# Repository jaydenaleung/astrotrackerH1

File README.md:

# Astrotracker H1
Astrotracker H1 is a DIY star tracker camera mount for astrophotography, made to open access to astrophotography without needing to purchase a more expensive star tracker. Includes a multi-axis rotational gimbal, automatic North Pole alignment, and possible upcoming GoTo integration.

FULL VIDEO DEMO: [https://youtu.be/irbhYrVtJVo](https://youtu.be/irbhYrVtJVo)

Onshape (CAD Model) Link: [https://cad.onshape.com/documents/bffc36d0f5bca770a27c02a3/w/2a2e8752598234cf6c653f02/e/8318d06d3c2c905c2b13cb54?renderMode=0&uiState=6adab1f747cc560a7bd789e2](https://cad.onshape.com/documents/bffc36d0f5bca770a27c02a3/w/2a2e8752598234cf6c653f02/e/8318d06d3c2c905c2b13cb54?renderMode=0&uiState=6adab1f747cc560a7bd789e2)

# Figures

**Total Minimum Cost:** $220 USD

**Total Hours Spent:** 135 hrs

**Total Days Spent:** 33 days

*See JOURNAL.md and the BOM below for an in-depth explanation of these numbers.*

# Overview

Astrotracker H1 is a **budget-friendly, custom star tracker** I built for the highest tier of [Hack Club's Highway "You Ship We Ship" program](https://highway.hackclub.com/). Star trackers assist long exposures in astrophotography by rotating the camera along the rotation of the stars, at **15°/hr**, to eliminate star trails from photos. This device attempts to solve these issues by **upgrading the traditional equatorial mount** to include a **polar scope** for precise alignment, a **counterweight** to balance the camera's weight, **automatic computerized alignment** using azimuthal and latitude (GPS) measurements, and a standard 1/4" tripod mount.

The device uses two plates connected by a hinge and a rotating gear. The bottom plate is the swivel plate, which adjusts the azimuthal heading of the device with a **high-torque motor**. The other plate is the rotational axis (RA) plate, which tilts to **match its angle of elevation to the device's GPS latitude** and is driven by a **precise worm gear with a 60:1 reduction ratio**. These mechanisms allow the device to automatically align with the North Pole, **calibrated using a precise polar scope**. Once the device is aligned, camera rotation will begin, driven by a **NEMA 17 stepper motor with microstepping**. Microstepping enhances these features by increasing the precision and resolution of the stepper motor by **up to 64 times**.

I like to approach my builds in three sections, something I learned from the Highway program: **CAD modeling, PCB design, and firmware**. For large mechanical projects like this, CAD often takes the most time. I model the entire physical assembly and create custom components in the **Onshape software**. Because of the size of the project, I made a **PCB "dashboard" with buttons connected to an ESP32 microcontroller**, and learned that complex PCBs often require multiple iterations! Finally, the **firmware used compass and GPS information** for auto-alignment and drove an LCD display on the dashboard showing the tracker's status.

# How It Works

The Three-Part Process
-

There are always three parts to an engineering project like this, at least for the Highway YSWS program. One is computer-aided design (CAD) modeling; for large projects, this often takes the most time, as it did with this project. Another is printed circuit board (PCB) design, which is the electrical component of the project. Finally, the brain of the build is programmed in the software part, where firmware is written onto a microcontroller that controls the hardware. See the pictures below for how I went about this!

CAD:

PCB:

Firmware:

Star Trackers
-

Since astrophotography is done in very dark environments, a long exposure ranging from a second to the whole night is needed. Due to Earth's rotation, keeping the camera in the same place for a long exposure causes the image to display star trails instead of clear, detailed stars. Star trackers fix this problem by rotating the camera on an equatorial mount aligned with the path of the stars, eliminating star trails. See this picture for a diagrammed explanation:

Astrotracker H1
-

This device attempts to solve these issues by upgrading the traditional equatorial mount to include a polar scope for precise alignment, a counterweight to balance the camera's weight, automatic computerized alignment using azimuthal and latitude (GPS) measurements, and a standard 1/4" tripod mount.

The mechanism is based on two plates connected by a hinge and a rotating gear. The bottom plate is the swivel plate, which swivels 360° and adjusts the azimuthal heading of the device. The other plate is the rotational axis (RA) plate, which tilts to match is angle of elevation to the device's GPS latitude and is driven by a precise worm gear. Matching the device's rotation to face exactly 0° north and its tilt to its GPS latitude allows the RA, the axis perpendicular to and in the middle of the rotating gear and the RA plate, to point exactly to the North Pole (next to the star Polaris). When the RA is pointed toward the North Pole and the rotating gear turns counterclockwise, the tracking will be able to accurately and precisely follow the path of the stars and prevent capturing star trails. Microstepping enhances these features by increasing the precision and resolution of the stepper motor by up to 64 times.

Additional Features
-

Apart from the bare-bones mechanism that drives the star tracker, these upgrades elevate the project to create a truly effective star tracker:
- Automatic, computerized alignment using GPS and compass data
- 1/16 and 1/64 microstepping for stepper motors
- Polar scope for precise adjustment
- Counterweight for balance
- Bubble level for precision
- Thrust and radial ball bearings for smooth rotation
- 12.5:1 reduction ratio for belt-driven rotating gear
- 60:1 reduction ratio for worm gear-driven hinge
- 51:1 reduction ratio for the gearbox on the stepper motor turning the swivel plate
- Organized PCB connecting everything on one board
- Standard 1/4" camera and tripod mount screws
- Ball mount to point camera the right way
- Center control console with up-down-left-right buttons for fine adjustment, start-stop tracking buttons, auto-adjustment capability, and a smart LCD UI interface

# The 'Why' Behind the Project
As an avid photographer and engineer myself, I have always wanted to get more involved with astrophotography. Unfortunately, living in a city didn't play out well for me because of the massive amount of light pollution around me, blocking my view of the stars. I knew I wanted to combine my passions, and the opportunity to do so came through Hack Club's Highway to Undercity program. They fund almost any project you propose to them through their You Ship We Ship (YSWS) initiative.

After conducting some research, I found out that a star tracker was one of the most necessary tools to take better pictures of the night sky. Unfortunately, they were all priced around $500 USD - a hefty investment. Building a star tracker would allow me to combine my passions and achieve a more cost-effective solution at the same time.

# Why This Is Worth Ten Points for Highway Program
This star tracker isn't just any star tracker or equatorial mount - it adds many more complex features that empower young photographers on a budget, like myself, to pursue astrophotography. Fundamentally, the project is already as mechanically complex as a six-point project without all of the additional features. The time spent building intricate features into the mechanical model, custom footprints into the PCB, and special features into the firmware truly takes this project above and beyond the guidelines for a six-point project. 

Not only did I pay attention to the detail and precision needed for such a device with the bubble level, high reduction ratios, and microstepping, but I also considered what would take this above its minimum viable product by adding complex logic for auto-alignment, a balancing counterweight to increase control, and an intuitive LCD user interface controlled with standard pushbuttons. Being able to connect all the electrical components on a single, thought-out PCB and the firmware logic for tracking and auto-alignment indeed also makes this project electrically and computationally complex. Furthermore, I was able to achieve all of these features for under $300 USD when most market star trackers cost about $500 USD. Finally, I spent a ton of time perfecting every detail and feature, putting in almost sixty hours *before* building it (while the recommended minimum time spent for a ten-point project is fifty hours).

# **Bill of Materials (BOM):**

*Note: I am using Aliexpress for some and Amazon for others. Prices listed below are in USD, per part, and rounded. e.g. 2x Nema 17 ($14) = $28 total. Also see the .csv file for the official BOM.*

| Quantity | Name | Price Per Part | Link |
| ----- | ------------ | ------ | -------------------------------------------- |
| 2x | Nema 17 stepper motor (regular) | $14 | [https://www.amazon.com/STEPPERONLINE-Stepper-Bipolar-Connector-compatible/dp/B00PNEQKC0](url) |
| 1x | Nema 17 stepper motor (w/gearbox) | $42 | [https://www.amazon.com/51-Planetary-Gearbox-Stepper-Precision/dp/B00QEVLDVO](url) |
| 1x | F8-22M thrust ball bearing | $1 | [https://www.aliexpress.us/item/3256807051413217.html](url) |
| 1x | 10-pack radial ball bearing, 3mm bore | $2 | [https://www.aliexpress.us/item/3256807605344885.html](url) |
| 1x | Worm gear set (worm + gear) | $12 | [https://www.amazon.com/uxcell-Worm-Gear-Set-Reduction/dp/B0DFCVKXLX](url) |
| 1x | PCB board (through JLCPCB & Hack Club $20 Coupon) | $0, covered by coupon | See gerbers.zip in 'pcb' folder |
| 1x | 20-pack 6x6x14 pushbutton | $1 | [https://www.aliexpress.us/item/2255800980685095.html](url) |
| 1x | I2C 16x2 LCD with I2C backpack, blue color | $1 | [https://www.aliexpress.us/item/3256808568663888.html](url) |
| 1x | ESP32 DEVKIT WROOM-32 38-Pin Development Board Type-C | $1 | [https://www.aliexpress.us/item/3256808295104972.html](url) |
| 1x | Resistor pack | $5 | [https://www.amazon.com/Resistor-Resistors-Assortment-Breadboard-Electronics/dp/B0F4P352BB](url) |
| 1x | NEO-8M GPS Module | $1 | [https://www.aliexpress.us/item/3256806859439052.html](url) |
| 1x | QMC5883L Compass Module | $2 | [https://www.aliexpress.us/item/3256807913730129.html](url) |
| 3x | TMC2209 stepper motor driver | $1 | [https://www.aliexpress.us/item/3256808046478114.html](url) |
| 1x | 16T 5mm bore gear | $7 | [https://www.amazon.com/WINSINN-Aluminum-Synchronous-Timing-Printer/dp/B077GMR328](url) |
| 1x | 16T toothless idler bearing for 6mm width GT2 belt, 3mm bore | $9 | [https://www.amazon.com/WINSINN-Aluminum-Timing-Toothless-Printer/dp/B07BPHPYTN?th=1](url) |
| 1x | 2-pack GT2 6mm width belt, 530mm length | $7 | [https://www.aliexpress.us/item/3256808983126633.html?gatewayAdapt=glo2usa4itemAdapt](url) |
| 1x | Polar scope | $27 | [https://www.amazon.com/Tydeux-Polar-Telescope-Finderscope-EQ-5/dp/B0D2L11C4G/](url) |
| 1x | 3-pack 1/4" camera screw | $1 | [https://www.aliexpress.us/item/3256806761503223.html](url) |
| 1x | Camera ball joint mount, red color | $1 | [https://www.aliexpress.us/item/3256802805830814.html](url) |
| 1x | 5-pack bubble level, 18x9mm | $1 | [https://www.aliexpress.us/item/3256808611329580.html](url) |
| 4x | 200g counterweight | $1 | [https://www.aliexpress.us/item/3256807217165073.html](url) |
| 1x | 6S LiPo battery, 22.2V 1000mAh 100C, XT60 connector | $15 | [https://www.amazon.com/Ovonic-Battery-1000mAh-Connector-CINEWHOOP/dp/B07JPK99D9](url) |
| 1x | XT60 male and female plug pack wires, 14 AWG, 15cm length | $1 | [https://www.aliexpress.us/item/3256808104814371.html](url) |
| 1x | LiPo battery charger | $30 | [https://www.amazon.com/B6-Battery-Charger-Discharger-Connectors/dp/B0F2H3XR6S](url) |
| 1x | M4 nuts and bolts, 270 pcs | $9 | [https://www.amazon.com/Kadrick-Assortment-Metric-Washers-Upgrade/dp/B0BZ6XG8PT?th=1](url) |
| 4x | M3 50pcs bolts, 6mm, 12mm, 16mm, 35mm versions | $1 | [https://www.aliexpress.us/item/2255800794906149.html](url) |
| 1x | M3 50 pcs hex nuts | $1 | [https://www.aliexpress.us/item/3256807407546447.html](url) |
| 1x | M2.5x30mm 50pcs bolts | $1 | [https://www.aliexpress.us/item/2255799955713291.html](url) |
| 1x | M2.5 50 pcs nuts | $1 | [https://www.aliexpress.us/item/3256807407546447.html](url) |
| 1x | Allen key set | $1 | [https://www.aliexpress.us/item/3256807283413035.html](url) |
| 1x | Long-nosed plier | $1 | [https://www.aliexpress.us/item/3256805792649837.html](url) |

| **Total minimum cost** | $220 |
| ---------------------- | ----- |
| **Total including 'in-case' of price changes, spare parts, etc.** | ~$235 |
| **Total including in-cases, sales tax (assumed ~6%), import and customs fees, etc.** | ~$270 |

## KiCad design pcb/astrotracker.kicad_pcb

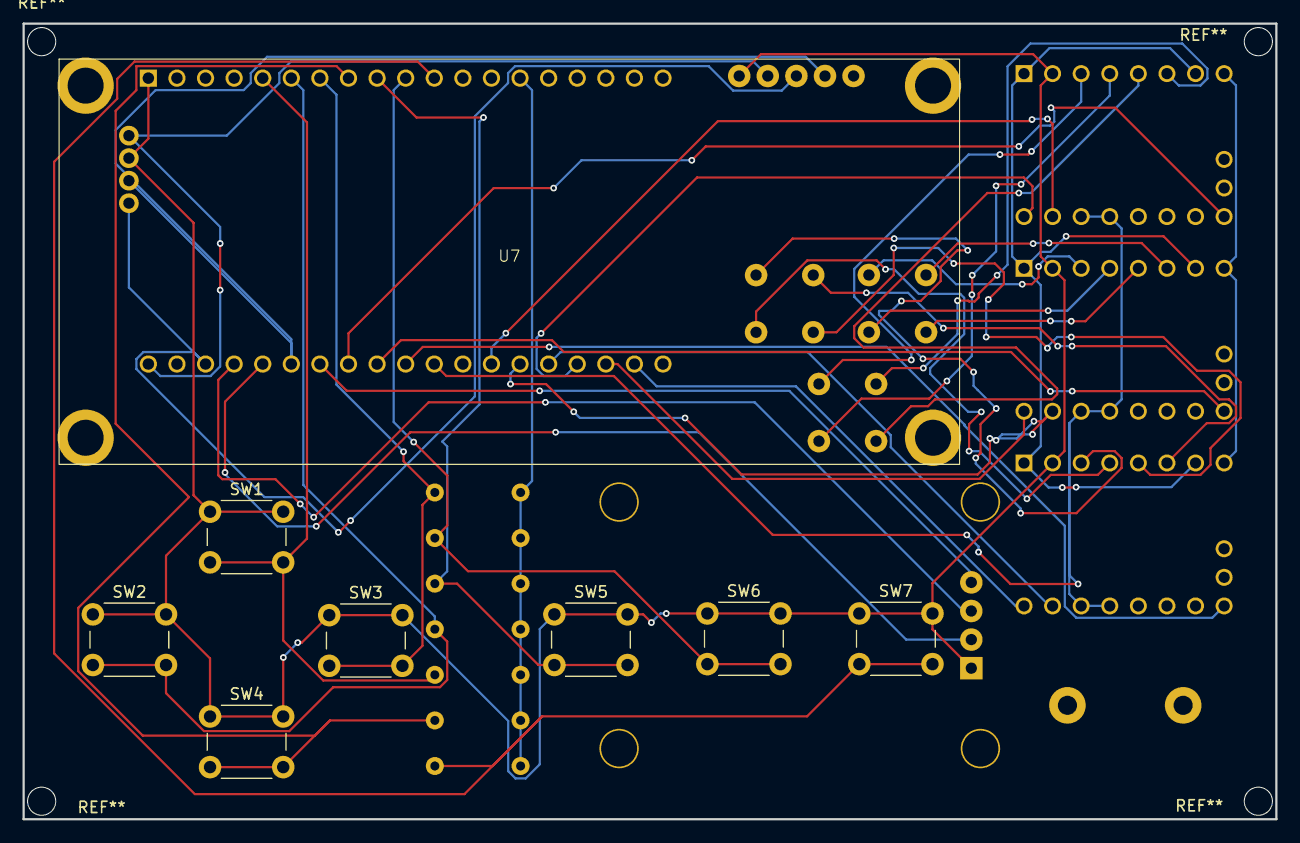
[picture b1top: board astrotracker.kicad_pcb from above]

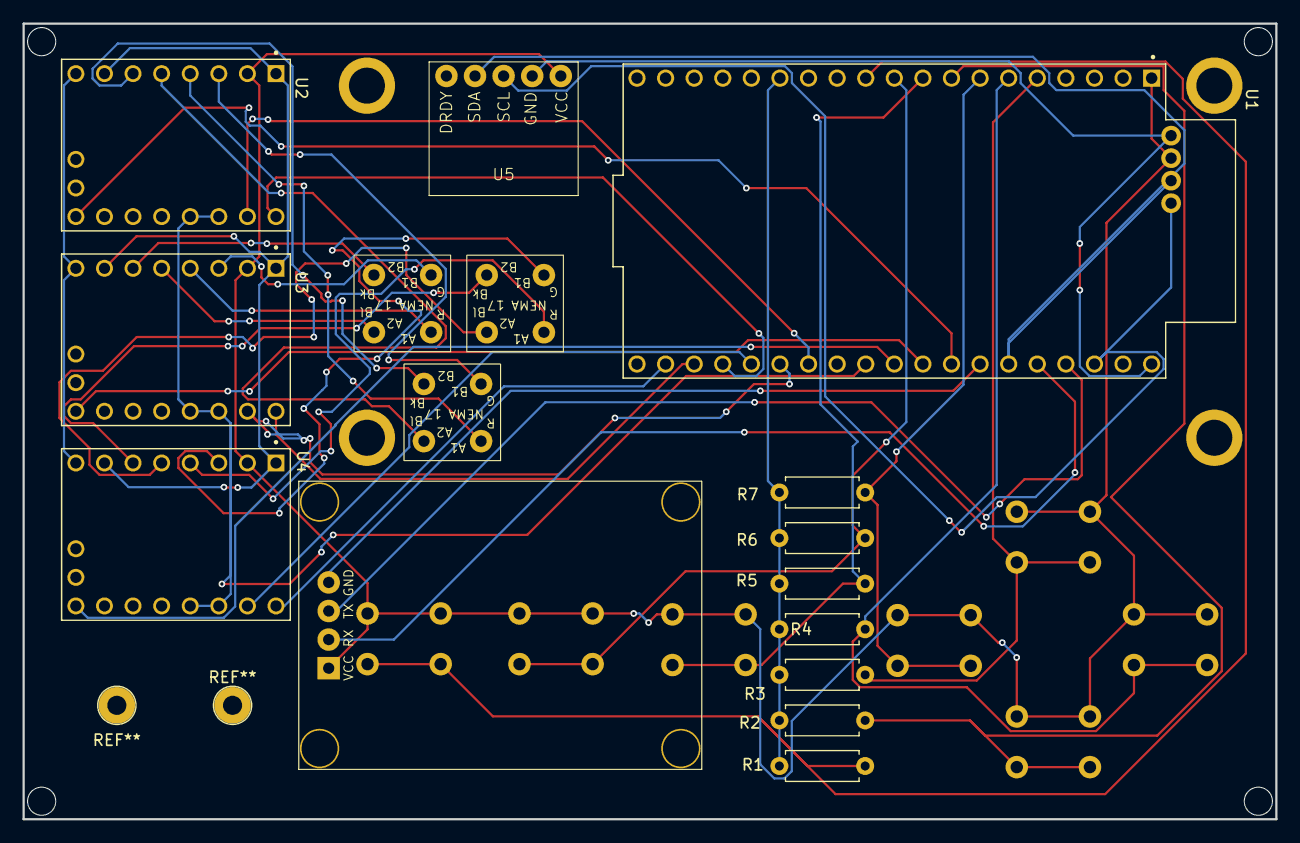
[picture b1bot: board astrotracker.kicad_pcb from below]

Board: 2 copper layers, 111.3 x 70.7 mm, 24 parts (16 on the bottom side), 39 nets.

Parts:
M1, M2, M3: Stepper_Motor_bipolar; NEMA-17
R1, R2, R3, R4, R5, R6, R7: 10K; R_Axial_DIN0207_L6.3mm_D2.5mm_P7.62mm_Horizontal
SW1, SW2, SW3, SW4, SW5, SW6, SW7: SW_Push; SW_PUSH_6mm
U1: DEVKIT_V1_ESP32-WROOM-32; MODULE_DEVKIT_V1_ESP32-WROOM-32
U2, U3, U4: TMC2209_SILENTSTEPSTICK; MODULE_TMC2209_SILENTSTEPSTICK
U5: QMC5883L_COMPASS; QMC5883L
U6: NEO-8M; GPS NEO-8M
U7: i2c_LCD

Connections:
+22.2V-25.2V (6S LiPo): U2.8 (VM), U3.8 (VM), U4.8 (VM)
GND (6S LiPo): U2.1 (GND), U2.7 (GND), U3.1 (GND), U3.7 (GND), U4.1 (GND), U4.7 (GND)
unnamed: M1.2 (-), U2.5 (M2A)
unnamed: M2.2 (-), U3.5 (M2A)
unnamed: M3.2 (-), U4.5 (M2A)
unnamed: SW1.1, SW2.1, SW3.1, SW4.1, SW5.1, SW6.1, SW7.1, U1.1 (3V3), U2.2 (VIO), U3.2 (VIO), U4.2 (VIO), U5.5 (VCC), U6.1 (VCC), U7.2 (VCC)
unnamed: R1.2, R2.2, R3.2, R4.2, R5.2, R6.2, R7.2, U1.14 (GND1)
unnamed: U1.32 (GND2), U6.4 (GND)
unnamed: U1.38 (GND3), U5.4 (GND), U7.1 (GND)
unnamed: U1.25 (IO0), U3.10 (STEP)
unnamed: U1.24 (IO2), U4.10 (STEP)
unnamed: U1.26 (IO4), U2.10 (STEP)
unnamed: U1.29 (IO5), U4.16 (~EN)
unnamed: U1.23 (IO15), U2.9 (DIR)
unnamed: U1.28 (IO17), U2.11 (PDN), U2.12 (UART), U3.11 (PDN), U3.12 (UART), U4.11 (PDN), U4.12 (UART)
unnamed: U1.30 (IO18), U3.16 (~EN)
unnamed: U1.31 (IO19), U2.16 (~EN)
unnamed: U1.33 (IO21), U5.2 (SDA), U7.3 (SDA)
unnamed: U1.36 (IO22), U5.3 (SCL), U7.4 (SCL)
unnamed: R5.1, SW5.2, U1.9 (IO25)
unnamed: R6.1, SW6.2, U1.10 (IO26)
unnamed: R1.1, SW7.2, U1.11 (IO27)
unnamed: R7.1, SW3.2, U1.7 (IO32)
unnamed: R2.1, SW4.2, U1.8 (IO33)
unnamed: R3.1, SW1.2, U1.5 (IO34)
unnamed: R4.1, SW2.2, U1.6 (IO35)
unnamed: U1.34 (RXD0), U6.2 (RX)
unnamed: U1.21 (SD0), U4.9 (DIR)
unnamed: U1.22 (SD1), U3.9 (DIR)
unnamed: U1.35 (TXD0), U6.3 (TX)
unnamed: M1.1, U2.4 (M1A)
unnamed: M1.3, U2.3 (M1B)
unnamed: M1.4, U2.6 (M2B)
unnamed: M2.1, U3.4 (M1A)
unnamed: M2.3, U3.3 (M1B)
unnamed: M2.4, U3.6 (M2B)
unnamed: M3.1, U4.4 (M1A)
unnamed: M3.3, U4.3 (M1B)
unnamed: M3.4, U4.6 (M2B)

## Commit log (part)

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2025-06-16 june 11th journal
2025-06-16 add pictures 6-11
2025-06-25 pcb design
2025-06-25 update pcb libraries
2025-06-25 finish pcb
2025-06-25 commit pcb
2025-06-25 Update fp-info-cache
2025-06-26 code
2025-06-29 FINISH PCB CAD
2025-06-30 complete cad folder
2025-07-01 test
2025-07-01 revert test
2025-07-01 final (hopefully)
2025-07-01 organization + final commit!! before submitting
2025-07-01 last commit
2025-07-07 update gerbers
2025-07-16 update cad
2025-07-16 cad upadte
2025-07-16 added gcodes
2025-07-27 update firmware
2025-08-04 add schematic to readme
2025-08-08 Update JOURNAL.md ADD PHOTOS
2025-08-14 ADD DEMO LINK
